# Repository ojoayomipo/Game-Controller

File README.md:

# Game-Controller
This repository includes the Gerber files, schematic diagram and PCB designs of a game controller

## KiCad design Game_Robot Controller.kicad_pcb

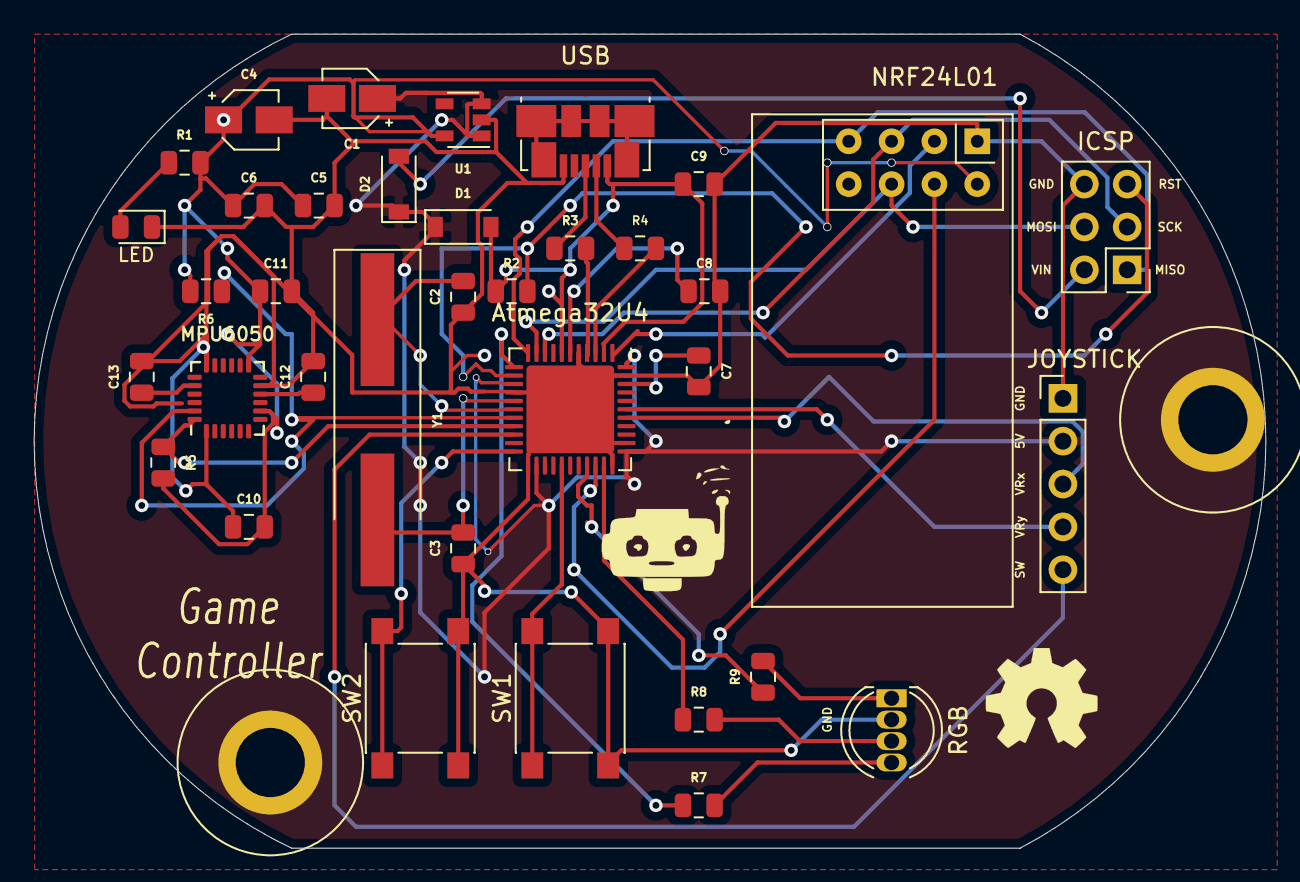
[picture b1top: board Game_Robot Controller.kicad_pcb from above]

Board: 2 copper layers, 73.0 x 48.3 mm, 36 parts (0 on the bottom side), 35 nets.

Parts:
Atmega32U4: ATmega32U4-MU; QFN-44-1EP_7x7mm_P0.5mm_EP5.2x5.2mm
C1: CP1_Small; CP_Elec_3x5.3
C2, C3: 22pF; C_0805_2012Metric
C4: 10uF; CP_Elec_3x5.3
C5, C8: 1uF; C_0805_2012Metric
C6, C7, C9, C11, C12: 0.1uF; C_0805_2012Metric
C10: 0.01uF; C_0805_2012Metric
C13: 2.2nF; C_0805_2012Metric
D1, D2: D_Schottky; D_SOD-123
ICSP: AVR-ISP-6; PinHeader_2x03_P2.54mm_Vertical
JOYSTICK: JoystickB; PinHeader_1x05_P2.54mm_Vertical
LED: LED; LED_0805_2012Metric
MPU6050: MPU-6050; InvenSense_QFN-24_4x4mm_P0.5mm
NRF24L01: NRF24L01_Breakout; nRF24L01_Breakout
R1: 1k; R_0805_2012Metric
R2: 10k; R_0805_2012Metric
R3, R4: 22R; R_0805_2012Metric
R5, R6: 4.7k; R_0805_2012Metric
R7, R8, R9: 220; R_0805_2012Metric
RGB: LED_RCBG; LED_D5.0mm-4_RGB
SW1, SW2: SW_Push; SW_SPST_PTS645
U1: MIC5219-3.3YM5; SOT-23-5
USB: USB_B_Micro; USB_Micro-B_Molex_47346-0001
Y1: Crystal; Crystal_SMD_HC49-SD_HandSoldering

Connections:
3.3V: C4.1, C5.1, C6.1, C10.2, C11.1, MPU6050.8, MPU6050.13, NRF24L01.2, R1.2, R5.2, R6.2, U1.5
5V: Atmega32U4.14, Atmega32U4.24, Atmega32U4.34, Atmega32U4.44, C1.1, D1.1, D2.1, JOYSTICK.2, U1.1, U1.3
A2: Atmega32U4.38, JOYSTICK.3
A3: Atmega32U4.39, JOYSTICK.4
CE: Atmega32U4.1, NRF24L01.3
CSN: Atmega32U4.31, NRF24L01.4
D0: Atmega32U4.20, JOYSTICK.5
D4: Atmega32U4.22, SW2.1
D6: Atmega32U4.27, SW1.1
D10: Atmega32U4.30, R9.1
D11: Atmega32U4.12, R7.1
D13: Atmega32U4.32, R8.1
D+: Atmega32U4.4, R3.2
D-: Atmega32U4.3, R4.2
GND: Atmega32U4.5, Atmega32U4.15, Atmega32U4.23, Atmega32U4.33, Atmega32U4.35, Atmega32U4.43, Atmega32U4.45, C1.2, C2.1, C3.1, C4.2, C5.2, C6.2, C7.2, C8.2, C9.2, C10.1, C11.2, C12.2, C13.2, ICSP.6, JOYSTICK.1, LED.1, MPU6050.1, MPU6050.11, MPU6050.18, NRF24L01.1, RGB.2, SW1.2, SW2.2, U1.2, USB.5
MISO: Atmega32U4.11, ICSP.1, NRF24L01.7
MOSI: Atmega32U4.10, ICSP.4, NRF24L01.6
unnamed: Atmega32U4.42, C7.1
unnamed: Atmega32U4.6, C8.1
unnamed: C12.1, MPU6050.10
unnamed: C13.1, MPU6050.20
unnamed: LED.2, R1.1
unnamed: R9.2, RGB.1
unnamed: R8.2, RGB.3
unnamed: R7.2, RGB.4
unnamed: R4.1, USB.2
unnamed: R3.1, USB.3
RST: Atmega32U4.13, ICSP.5, R2.2
SCK: Atmega32U4.9, ICSP.3, NRF24L01.5
SCL: Atmega32U4.18, MPU6050.23, R6.1
SDA: Atmega32U4.19, MPU6050.24, R5.1
VBUS: Atmega32U4.2, Atmega32U4.7, C9.1, D1.2, R2.1, USB.1
VIN: D2.2, ICSP.2
XTAL1: Atmega32U4.17, C2.2, Y1.1
XTAL2: Atmega32U4.16, C3.2, Y1.2
